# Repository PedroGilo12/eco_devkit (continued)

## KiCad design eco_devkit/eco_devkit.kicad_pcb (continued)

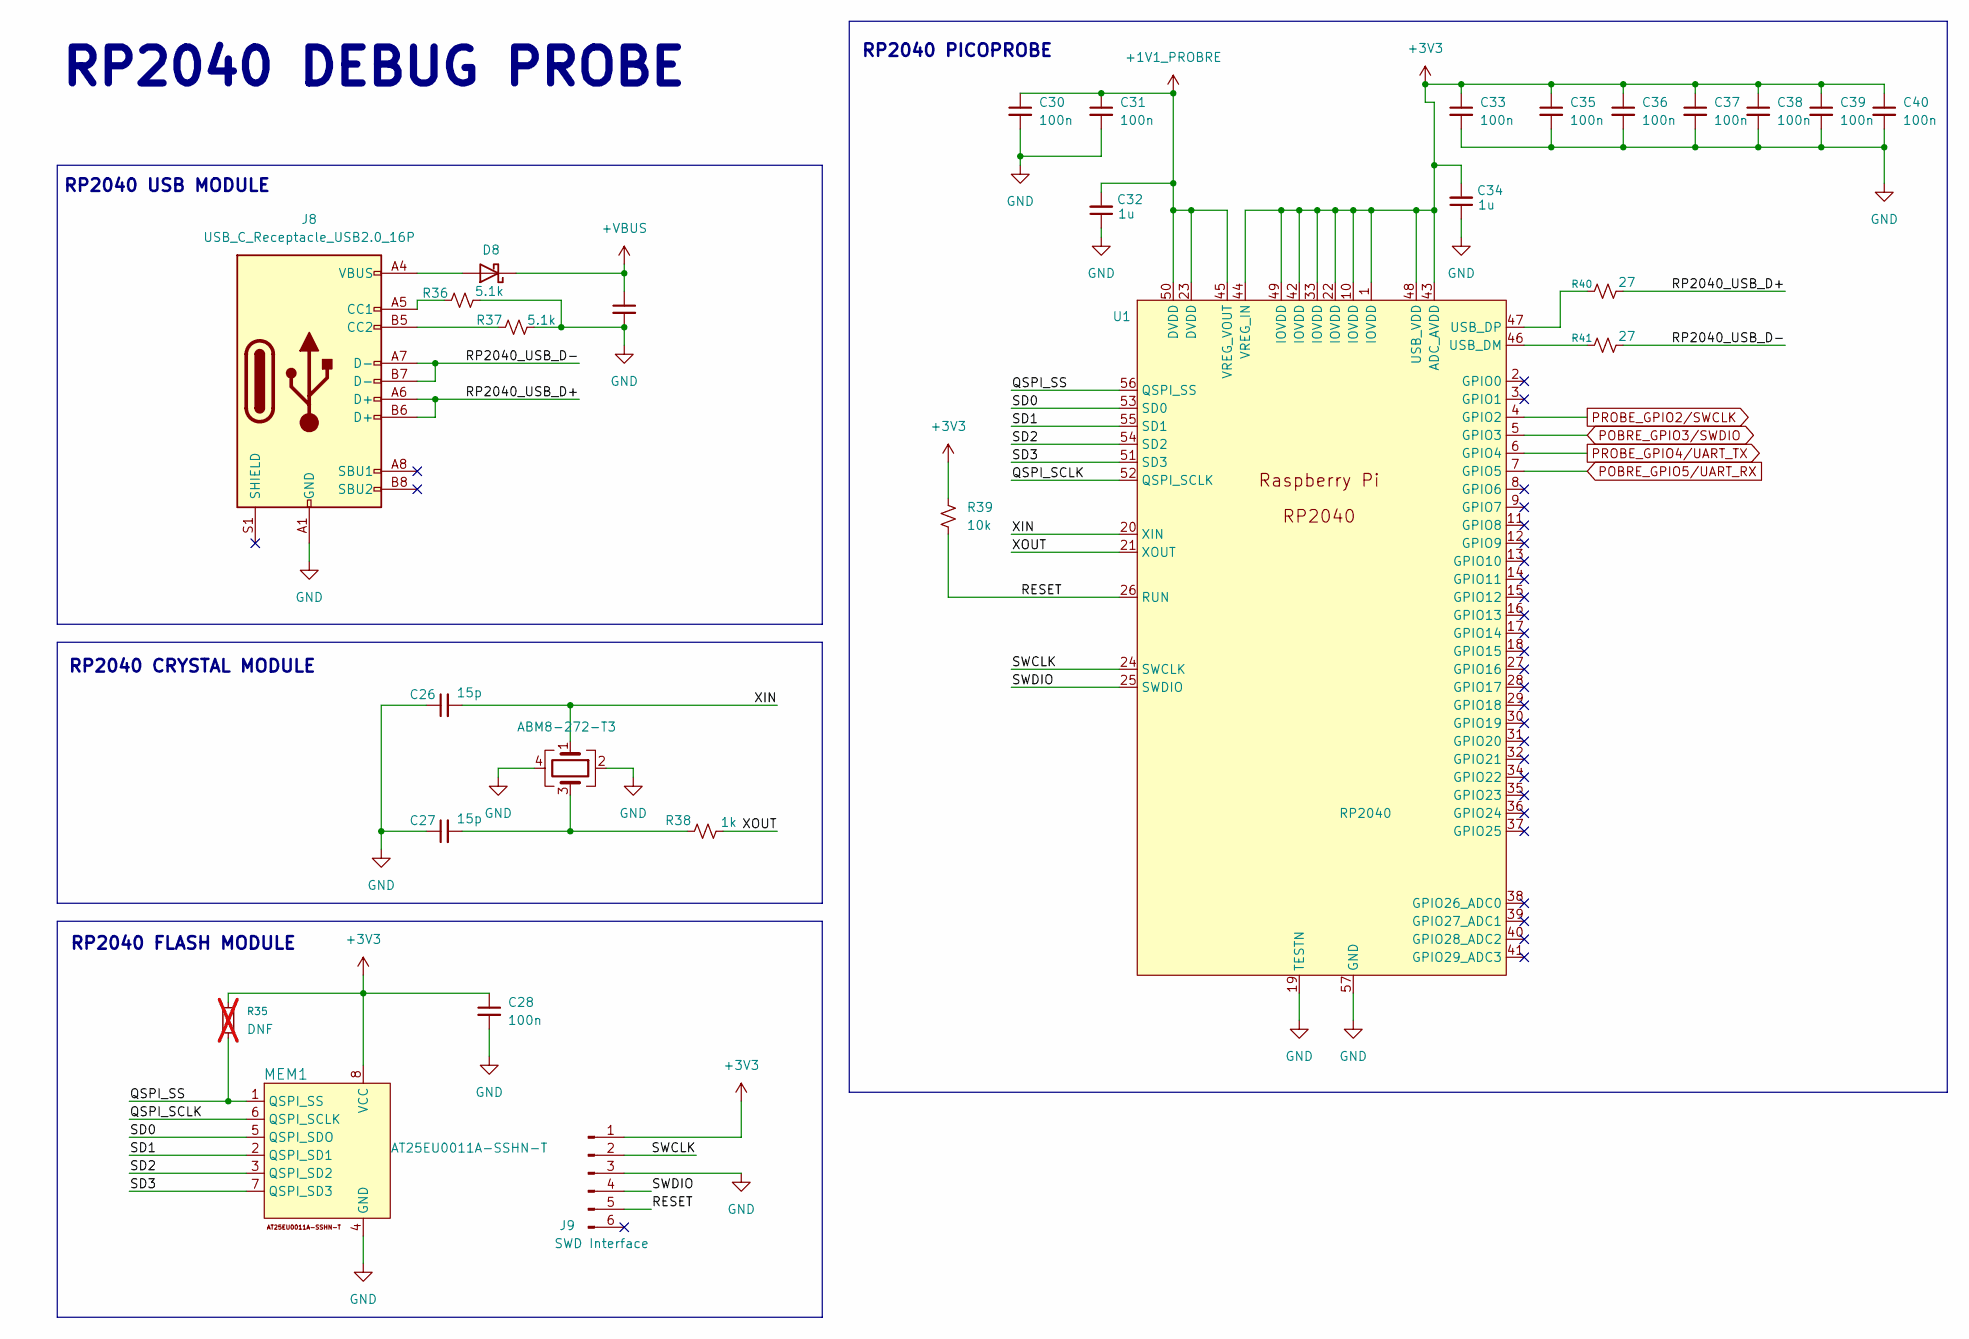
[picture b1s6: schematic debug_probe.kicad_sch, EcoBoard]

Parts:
C26, C27: 15p; C_0603_1608Metric; MPN C0603C150K8RACAUTO
C28, C30, C31, C33, C35, C36, C37, C38, C39, C40: 100n; C_0402_1005Metric; MPN 0402B104K250HI
C29: 10u; C_0402_1005Metric; MPN 0402W106M6R3HI
C32, C34: 1u; C_0402_1005Metric; MPN C1005X6S1C105K050EC
D8: SB120; D_SOD-123F; MPN SM5817PL-TP
J8: USB_C_Receptacle_USB2.0_16P; UJ20-C-H-G-SMT-1-P16-TR; MPN UJ20-C-H-G-SMT-1-P16-TR
J9: SWD Interface; PinSocket_1x06_P2.54mm_Vertical
MEM1: AT25EU0011A-SSHN-T; SOIC127P790X216-8N; MPN AT25EU0011A-SSHN-T
R35: DNF; R_0402_1005Metric; not fitted
R36, R37: 5.1k; R_0402_1005Metric; MPN RC0402FR-7W5K1L
R38: 1k; R_0402_1005Metric; MPN CRCW04021K00FKED
R39: 10k; R_0402_1005Metric; MPN CRGP0402F10K
R40, R41: 27; R_0402_1005Metric; MPN RCS040227R0FKED
U1: RP2040; QFN-56-1EP_7x7mm_P0.4mm_EP3.2x3.2mm_ThermalVias
Y2: ABM8-272-T3; MPN ABM8-272-T3

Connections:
+1V1_PROBRE: C30.1, C31.1, C32.2, U1.23 (DVDD), U1.45 (VREG_VOUT), U1.50 (DVDD)
+3V3: C28.1, C33.1, C34.2, C35.1, C36.1, C37.1, C38.1, C39.1, C40.1, J9.1, MEM1.8 (VCC), R35.2, R39.1, U1.1 (IOVDD), U1.10 (IOVDD), U1.22 (IOVDD), U1.33 (IOVDD), U1.42 (IOVDD), U1.43 (ADC_AVDD), U1.44 (VREG_IN), U1.48 (USB_VDD), U1.49 (IOVDD); also elsewhere on the board
+VBUS: C29.1, D8.1 (K); also elsewhere on the board
/Debug Probe/QSPI_SCLK: MEM1.6 (QSPI_SCLK), U1.52 (QSPI_SCLK)
/Debug Probe/QSPI_SS: MEM1.1 (QSPI_SS), R35.1, U1.56 (QSPI_SS)
/Debug Probe/RESET: J9.5, R39.2, U1.26 (RUN)
/Debug Probe/RP2040_USB_D+: J8.A6 (D+), J8.B6 (D+), R40.2
/Debug Probe/RP2040_USB_D-: J8.A7 (D-), J8.B7 (D-), R41.2
/Debug Probe/SD0: MEM1.5 (QSPI_SDO), U1.53 (SD0)
/Debug Probe/SD1: MEM1.2 (QSPI_SD1), U1.55 (SD1)
/Debug Probe/SD2: MEM1.3 (QSPI_SD2), U1.54 (SD2)
/Debug Probe/SD3: MEM1.7 (QSPI_SD3), U1.51 (SD3)
/Debug Probe/SWCLK: J9.2, U1.24 (SWCLK)
/Debug Probe/SWDIO: J9.4, U1.25 (SWDIO)
/Debug Probe/XIN: C26.2, U1.20 (XIN), Y2.1
/Debug Probe/XOUT: R38.2, U1.21 (XOUT)
GND: C26.1, C27.1, C28.2, C29.2, C30.2, C31.2, C32.1, C33.2, C34.1, C35.2, C36.2, C37.2, C38.2, C39.2, C40.2, J8.A1 (GND), J8.A12 (GND), J8.B1 (GND), J8.B12 (GND), J9.3, MEM1.4 (GND), R36.2, R37.2, U1.19 (TESTN), U1.57 (GND), Y2.2, Y2.4; also elsewhere on the board
unnamed: C27.2, R38.1, Y2.3
unnamed: D8.2 (A), J8.A4 (VBUS), J8.A9 (VBUS), J8.B4 (VBUS), J8.B9 (VBUS)
unnamed: J8.A5 (CC1), R36.1
unnamed: J8.B5 (CC2), R37.1
unnamed: R41.1, U1.46 (USB_DM)
unnamed: R40.1, U1.47 (USB_DP)
POBRE_GPIO3/SWDIO: U1.5 (GPIO3); also elsewhere on the board
POBRE_GPIO5/UART_RX: U1.7 (GPIO5); also elsewhere on the board
PROBE_GPIO2/SWCLK: U1.4 (GPIO2); also elsewhere on the board
PROBE_GPIO4/UART_TX: U1.6 (GPIO4); also elsewhere on the board

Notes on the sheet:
RP2040 USB MODULE
RP2040 DEBUG PROBE
RP2040 PICOPROBE
RP2040 CRYSTAL MODULE
RP2040 FLASH MODULE

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
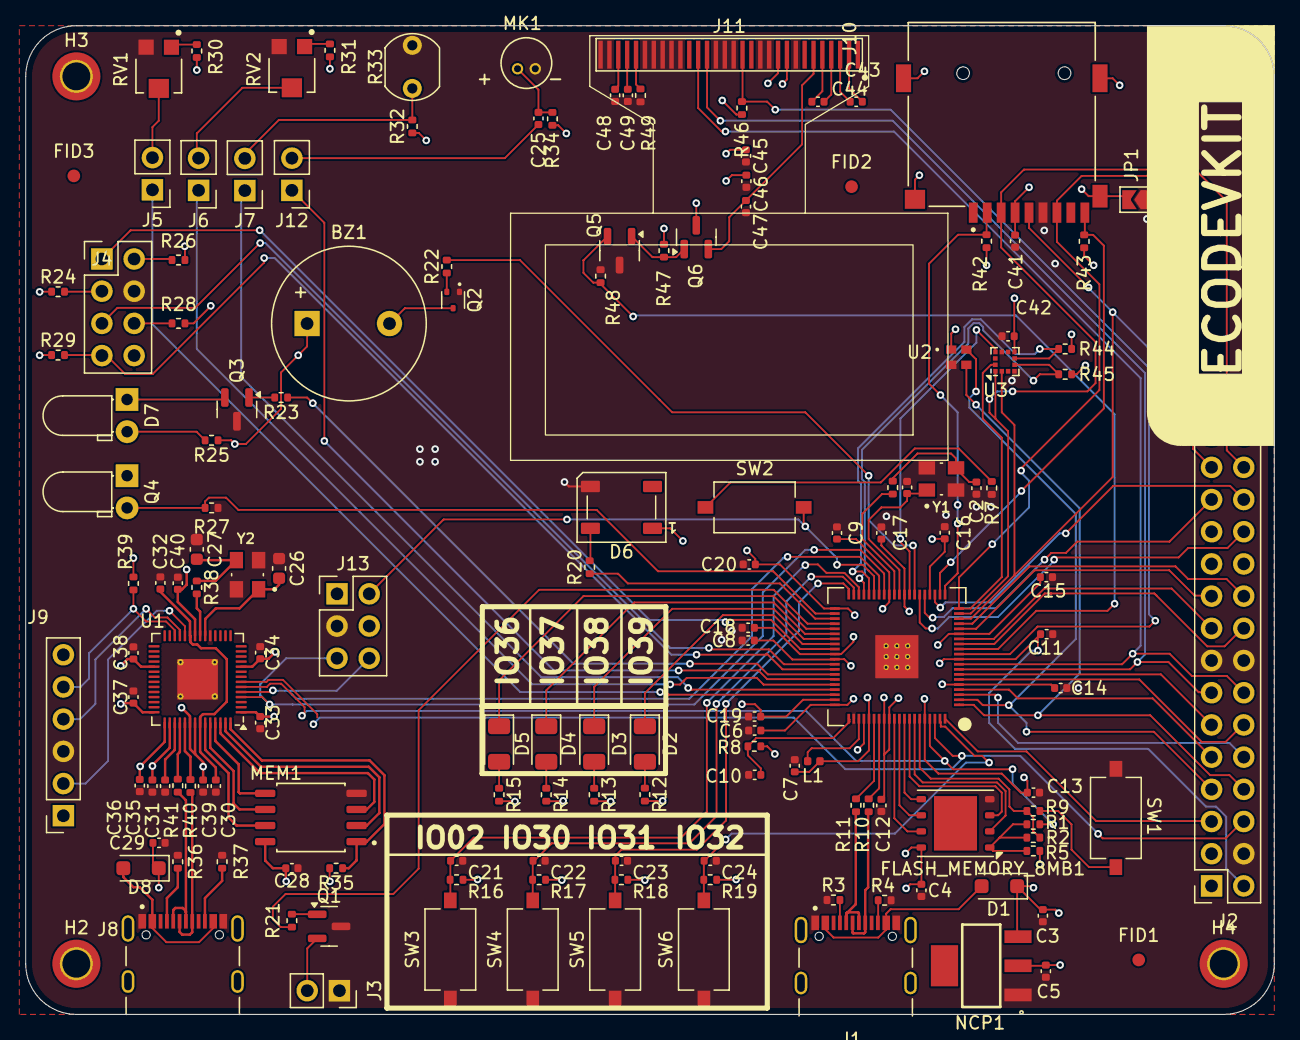
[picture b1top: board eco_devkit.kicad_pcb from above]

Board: 4 copper layers, 98.5 x 78.0 mm, 153 parts (0 on the bottom side), 128 nets.

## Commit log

2025-06-20 Inicia projeto.
2025-06-22 adding probe's lib and schematics
2025-06-22 Add analog peripherals.
2025-06-22 Add bg22 symbol library and update symbol library table
2025-06-22 att mpn e fotoprint da bg22
2025-06-22 feat: implement GPIO peripherals (buttons, LEDs, buzzer, MOSFET)
    - Infrared not included
2025-06-23 chore: ajustes nos periféricos GPIO e mapeamento do conector SWD
2025-06-23 Add SPI
2025-06-23 Add bluetooth.
2025-06-23 First interation.
2025-06-25 chore: ajustes nos periféricos
2025-06-26 Corrige periféricos 1.
2025-06-26 Cria arquivo de backup.
2025-06-26 added modules footprint and digikey datasheets & schematic adjustments
2025-06-27 Notate schematic.
2025-06-27 chore: Remove reference to bg22 symbol from sym-lib-table
2025-06-30 Atualizar o símbolo do display, por todos os pinos de um lado
2025-07-01 chore: Ajuste dos resistores de pull-up para Not Fitted e reorganização dos pinos do display
    - Atualizados os resistores de pull-up para status Not Fitted, considerando a possibilidade de uso de pull-ups internos do microcontrolador.
    - Reorganizados os pinos do display para que fiquem todos de um único lado, facilitando o roteamento da PCB.
2025-07-01 Corrige folha dos perifericos
2025-07-01 Adiciona footprints
2025-07-01 Atribui footprints.
2025-07-01 Corrige footprints.
2025-07-01 feat: ajustes de footprints e revisão de dimensões dos componentes
    - Confirmado footprint do slot de cartão SD.
    - Adicionado footprint para o sensor de luminosidade I2C (light sensor).
    - Adicionado footprint para o display SPI (conector FFC de 28 pinos).
    - Revisado e conferido as dimensões dos pads do acelerômetro (ACCEL), validando tamanho de cada área de contato.
2025-07-01 merging with the updated development branch
2025-07-01 refining adjustments on RP2350 and it's modules
2025-07-01 Add footprints
2025-07-01 changing global labels to local
2025-07-02 footprint completed
2025-07-02 feat: initial placement of MCU components
2025-07-02 feat: placement of MCU passive components and crystal
2025-07-03 Add layout
2025-07-03 Update layout
2025-07-03 feat: placement of I2C and SPI peripherals
2025-07-03 Add digital peripherals layout.
2025-07-03 feat: MCU placement and routing of power and signal connections
2025-07-03 Add probe.
2025-07-03 Placement v1.
2025-07-04 fix:adjustments to component placement and routing
2025-07-04 Add all nets
2025-07-04 Finish
2025-07-04 Penultimo
2025-07-06 chore: routing some PCB components
2025-07-07 routed all components except header and copper pours
2025-07-07 Finaliza projeto
